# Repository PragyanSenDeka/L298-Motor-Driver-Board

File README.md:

L298 Motor Driver with current sensing

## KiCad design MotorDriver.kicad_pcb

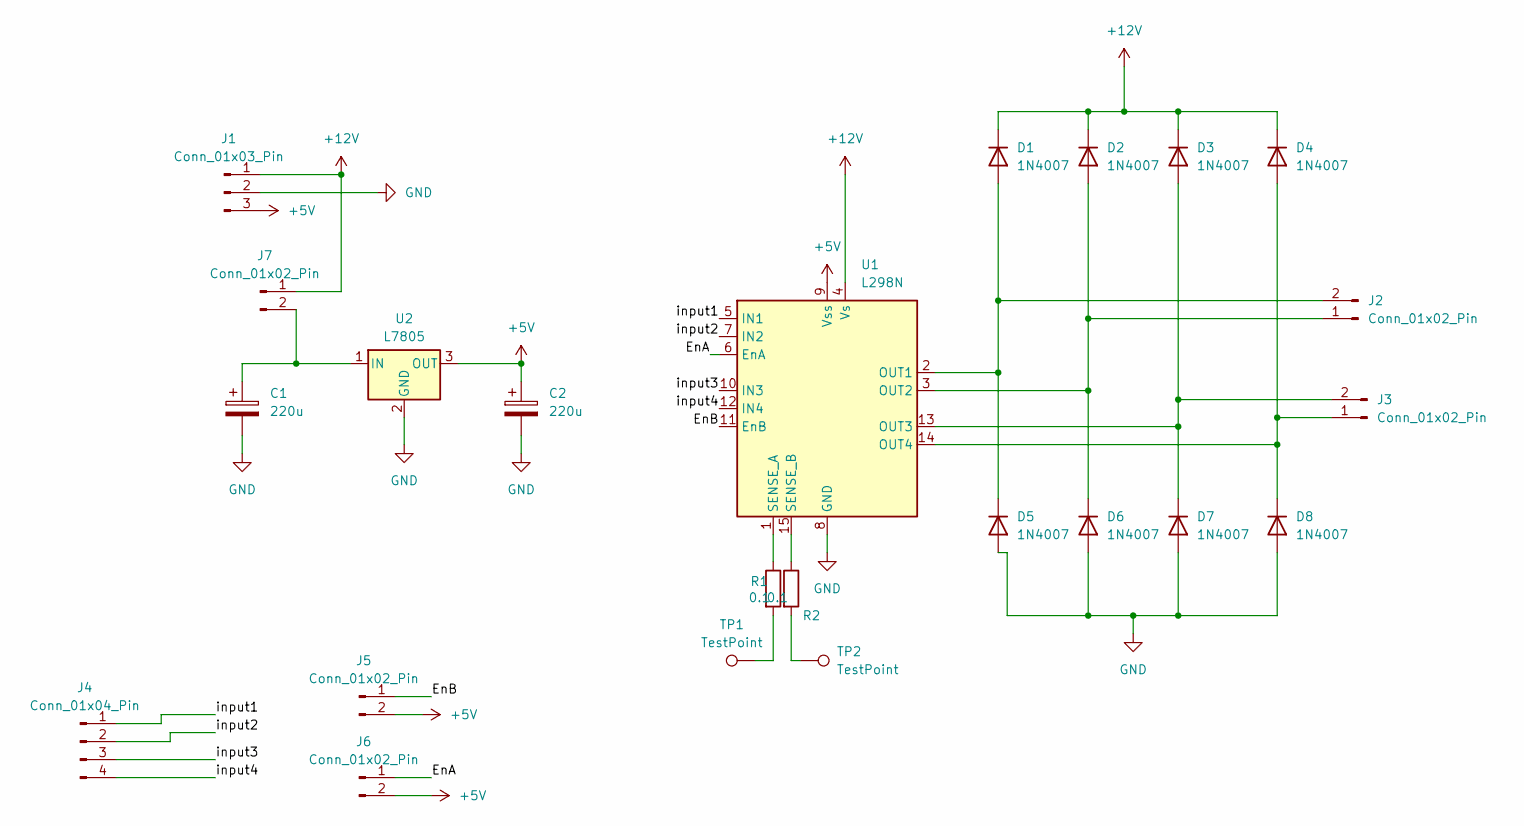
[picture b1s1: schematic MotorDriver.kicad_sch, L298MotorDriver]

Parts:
C1: 220u; CP_Radial_D10.0mm_P2.50mm
C2: 220u; CP_Axial_L26.5mm_D20.0mm_P33.00mm_Horizontal
D1, D2, D3, D4, D5, D6, D7, D8: 1N4007; D_DO-41_SOD81_P10.16mm_Horizontal
J1: Conn_01x03_Pin; TerminalBlock_Phoenix_MKDS-1,5-3_1x03_P5.00mm_Horizontal
J2, J3: Conn_01x02_Pin; TerminalBlock_Phoenix_MKDS-1,5-2_1x02_P5.00mm_Horizontal
J4: Conn_01x04_Pin; PinHeader_1x04_P2.54mm_Vertical
J5, J6, J7: Conn_01x02_Pin; PinHeader_1x02_P2.54mm_Vertical
R1, R2: 0.1; R_0201_0603Metric_Pad0.64x0.40mm_HandSolder
TP1, TP2: TestPoint; TestPoint_Keystone_5005-5009_Compact
U1: L298N; TO-220-15_P2.54x5.08mm_StaggerOdd_Lead4.58mm_Vertical
U2: L7805; TO255P1020X450X2000-3

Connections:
+5V: C2.1, J1.3, J5.2, J6.2, U1.9 (Vss), U2.3 (OUT)
+12V: D1.1 (K), D2.1 (K), D3.1 (K), D4.1 (K), J1.1, J7.1, U1.4 (Vs)
/EnA: J6.1, U1.6 (EnA)
/EnB: J5.1, U1.11 (EnB)
/input1: J4.1, U1.5 (IN1)
/input2: J4.2, U1.7 (IN2)
/input3: J4.3, U1.10 (IN3)
/input4: J4.4, U1.12 (IN4)
GND: C1.2, C2.2, D5.2 (A), D6.2 (A), D7.2 (A), D8.2 (A), J1.2, U1.8 (GND), U2.2 (GND)
unnamed: D1.2 (A), D5.1 (K), J2.2, U1.2 (OUT1)
unnamed: D2.2 (A), D6.1 (K), J2.1, U1.3 (OUT2)
unnamed: D3.2 (A), D7.1 (K), J3.2, U1.13 (OUT3)
unnamed: D4.2 (A), D8.1 (K), J3.1, U1.14 (OUT4)
unnamed: C1.1, J7.2, U2.1 (IN)
unnamed: R1.2, TP1.1
unnamed: R2.2, TP2.1
unnamed: R1.1, U1.1 (SENSE_A)
unnamed: R2.1, U1.15 (SENSE_B)

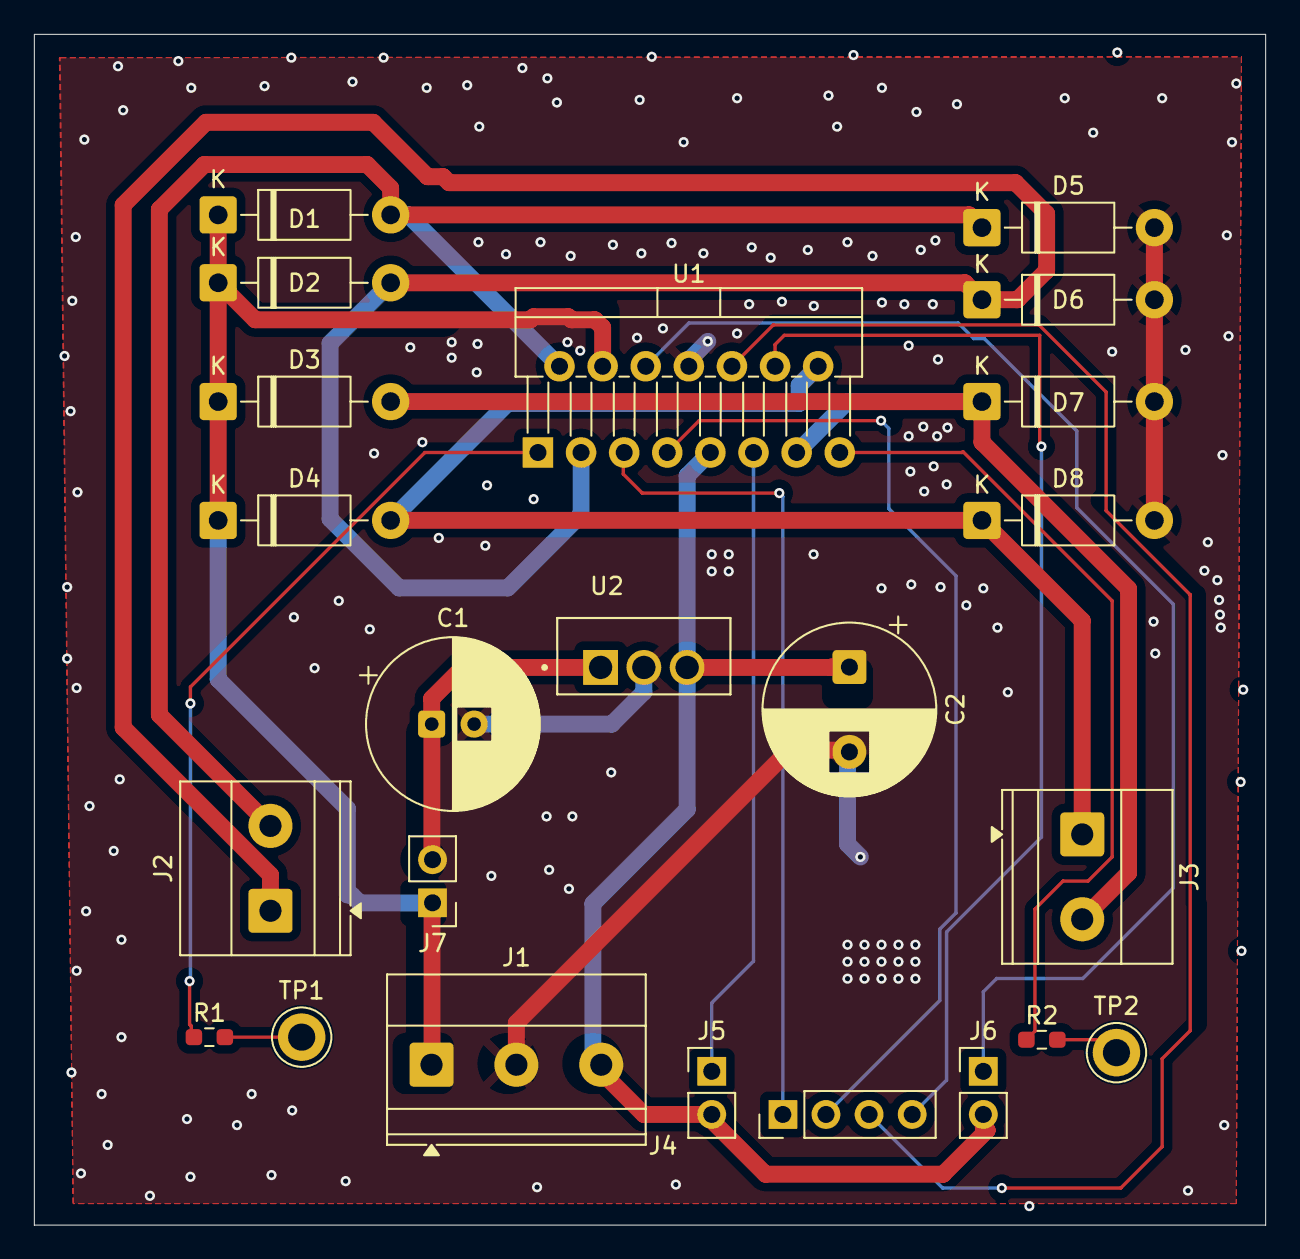
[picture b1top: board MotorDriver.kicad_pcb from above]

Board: 2 copper layers, 72.5 x 70.2 mm, 23 parts (0 on the bottom side), 18 nets.

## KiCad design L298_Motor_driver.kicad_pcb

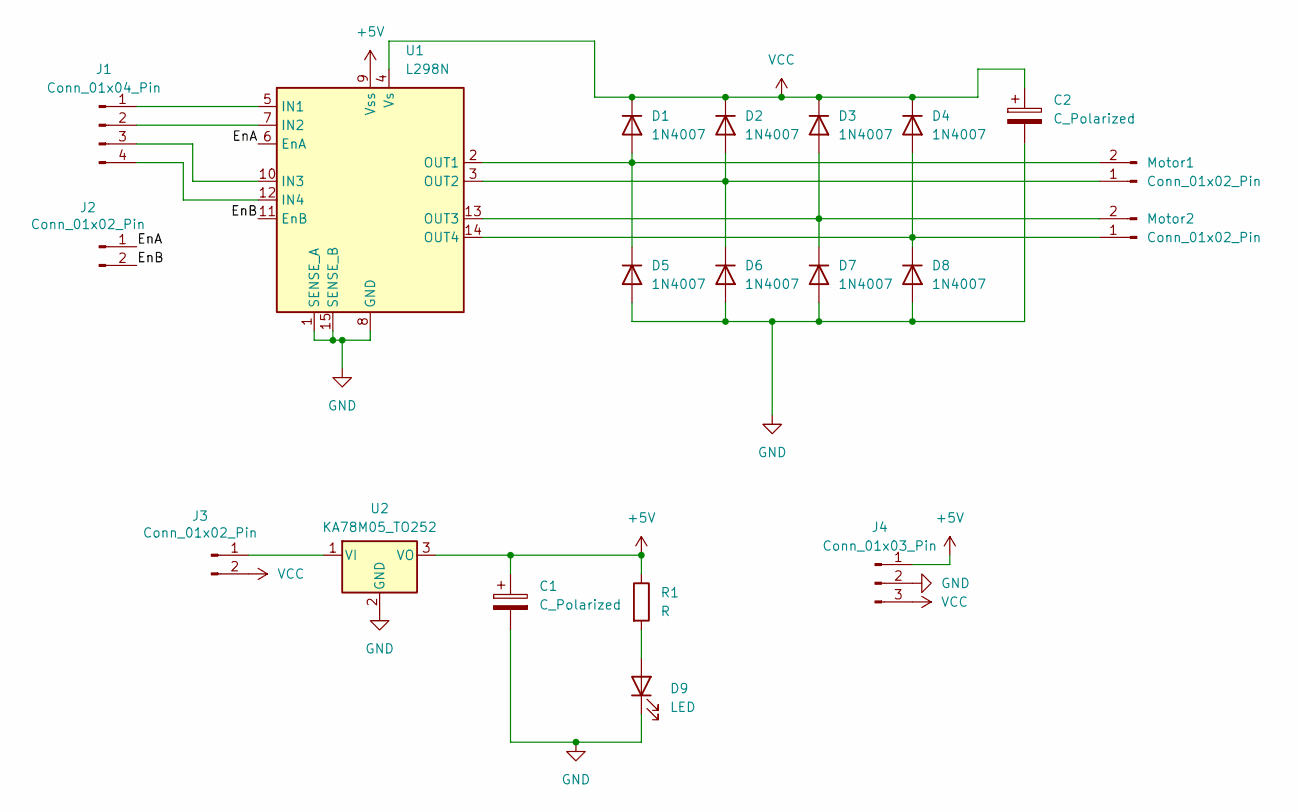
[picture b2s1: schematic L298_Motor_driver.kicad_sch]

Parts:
C1, C2: C_Polarized; CP_Radial_D5.0mm_P2.50mm
D1, D2, D3, D4, D5, D6, D7, D8: 1N4007; D_DO-41_SOD81_P10.16mm_Horizontal
D9: LED; LED_0201_0603Metric_Pad0.64x0.40mm_HandSolder
J1: Conn_01x04_Pin; PinHeader_1x04_P2.54mm_Vertical
J2: Conn_01x02_Pin; PinHeader_1x02_P2.54mm_Vertical
J3: Conn_01x02_Pin; PinHeader_1x02_P1.27mm_Vertical
J4: Conn_01x03_Pin; TerminalBlock_MaiXu_MX126-5.0-03P_1x03_P5.00mm
Motor1, Motor2: Conn_01x02_Pin; TerminalBlock_MetzConnect_Type086_RT03402HBLC_1x02_P3.81mm_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
R1: R; R_0201_0603Metric_Pad0.64x0.40mm_HandSolder
U1: L298N; TO-220-15_P2.54x5.08mm_StaggerOdd_Lead4.58mm_Vertical
U2: KA78M05_TO252; TO-252-2

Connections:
+5V: C1.1, J4.1, R1.1, U1.9 (Vss), U2.3 (VO)
/EnA: J2.1, U1.6 (EnA)
/EnB: J2.2, U1.11 (EnB)
GND: C1.2, C2.2, D5.2 (A), D6.2 (A), D7.2 (A), D8.2 (A), D9.1 (K), J4.2, U1.1 (SENSE_A), U1.8 (GND), U1.15 (SENSE_B), U2.2 (GND)
unnamed: D1.2 (A), D5.1 (K), Motor1.2, U1.2 (OUT1)
unnamed: D2.2 (A), D6.1 (K), Motor1.1, U1.3 (OUT2)
unnamed: D3.2 (A), D7.1 (K), Motor2.2, U1.13 (OUT3)
unnamed: D4.2 (A), D8.1 (K), Motor2.1, U1.14 (OUT4)
unnamed: D9.2 (A), R1.2
unnamed: J1.1, U1.5 (IN1)
unnamed: J1.2, U1.7 (IN2)
unnamed: J1.3, U1.10 (IN3)
unnamed: J1.4, U1.12 (IN4)
unnamed: J3.1, U2.1 (VI)
VCC: C2.1, D1.1 (K), D2.1 (K), D3.1 (K), D4.1 (K), J3.2, J4.3, U1.4 (Vs)

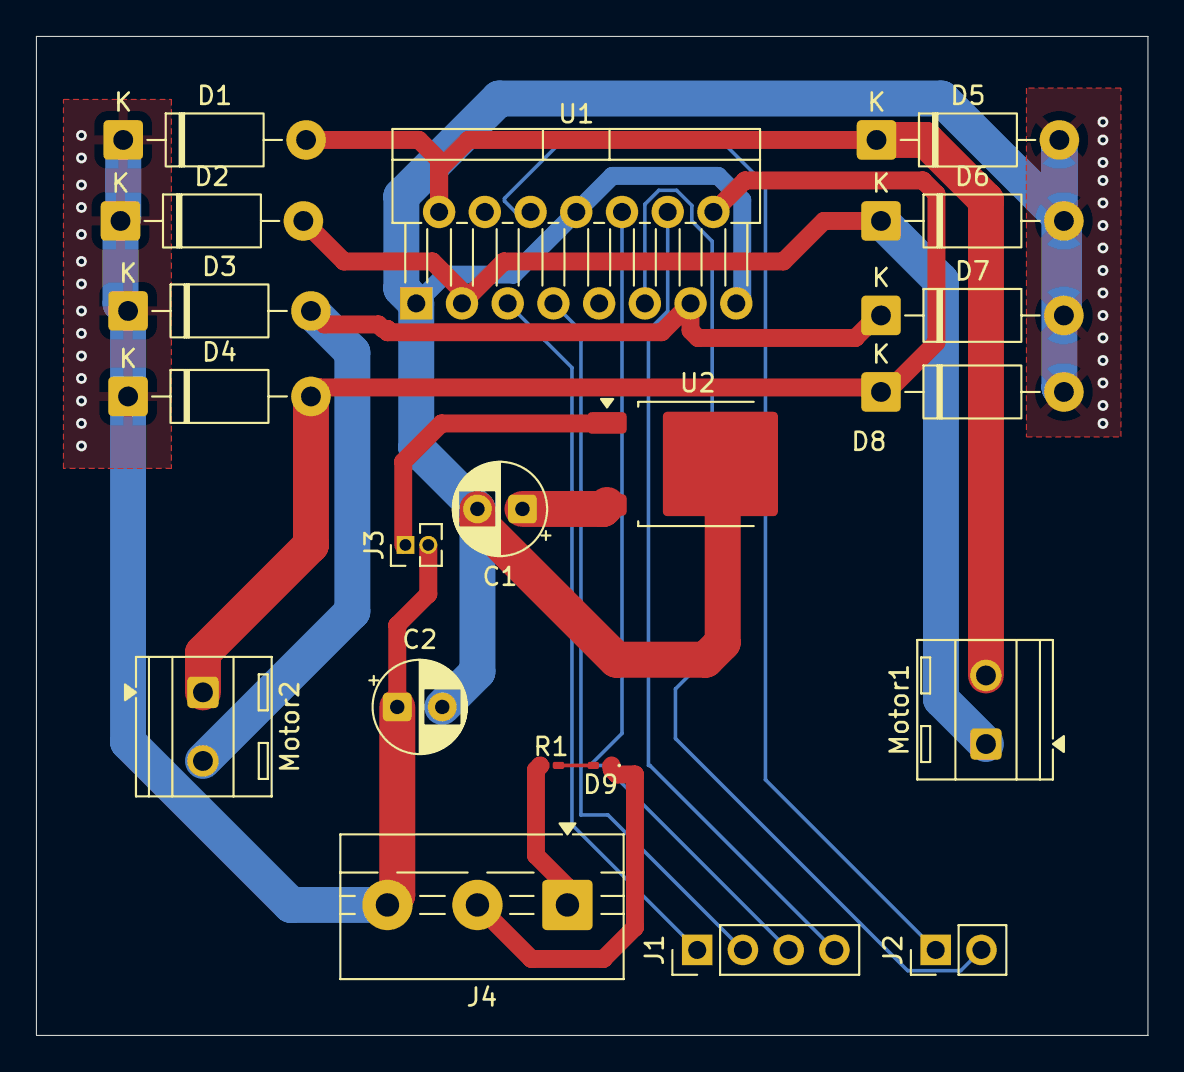
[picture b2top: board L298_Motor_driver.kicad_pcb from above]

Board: 2 copper layers, 61.8 x 55.5 mm, 20 parts (0 on the bottom side), 15 nets.

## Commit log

2026-01-29 project added
2026-03-18 Replaced with new files
